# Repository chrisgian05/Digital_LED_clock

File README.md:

# Digital LED Clock

A 6-digit 7-segment clock (HH:MM:SS) built around an ATmega328P, an
external RTC, and a constant-current LED driver — split across two
custom PCBs I designed in KiCad. This was mostly an excuse to actually
use everything I've learned so far about digital electronics and
embedded C in one project I could see and touch, instead of another
breadboard that gets torn down at the end of the semester.

## What it does

- Shows time as HH:MM:SS across 6 seven-segment digits
- Keeps time with a DS3231 RTC (accurate even when the board is
  powered off, thanks to a coin cell)
- 4 buttons: set hour, set minute, reset seconds, and toggle to show
  the DS3231's built-in temperature reading instead of the time
- Multiplexed display — only one digit is physically powered at a
  time, cycled fast enough (~166Hz) that it looks fully lit

## Hardware

Two boards, connected by a short ribbon cable:

- **`clock_board`** — the "brains." ATmega328P, DS3231 RTC, a 74HC595
  shift register + 6 transistors for digit selection, an ISP header
  for programming, and the 4 push buttons.
- **`led_board`** — the "face." A TLC5916 constant-current LED driver
  feeding three 2-digit common-anode 7-segment modules (6 digits
  total), plus the transistor-switched power lines coming in from the
  clock board.

Full schematics and PCB layouts are in [`hardware/`](hardware/), one
subfolder per board. Both were designed from scratch in KiCad — no
dev-board shields, no premade modules other than the RTC/driver ICs
themselves.

## Firmware

Bare-metal AVR C — no Arduino core, straight `avr-libc` and direct
register access. I wanted to actually deal with I2C, timers, and
interrupts myself instead of hiding behind `Wire.h` and `digitalWrite`.

- **`twi.c`** — hardware I2C driver for talking to the DS3231
- **`ds3231.c`** — RTC register access (BCD conversion, get/set time, temperature)
- **`display.c`** — 7-segment font table + the Timer1 interrupt that handles
  digit multiplexing (bit-banging both the 74HC595 and TLC5916 shift chains)
- **`buttons.c`** — debounced button reads with auto-repeat on hold
- **`main.c`** — main loop tying it all together

All of it lives in [`firmware/`](firmware/), buildable with either the
included `Makefile` or `platformio.ini`.

## Status

Schematics and PCBs are designed; firmware is written and reviewed but
**not yet validated on the assembled board** (still waiting on
boards/soldering as of writing this). A couple of polarity assumptions
(digit-select active-high/low, segment driver active-high/low) are
flagged with `#define`s in `firmware/src/config.h` specifically because
they're easier to confirm with a multimeter on the real board than to
guess from a schematic.

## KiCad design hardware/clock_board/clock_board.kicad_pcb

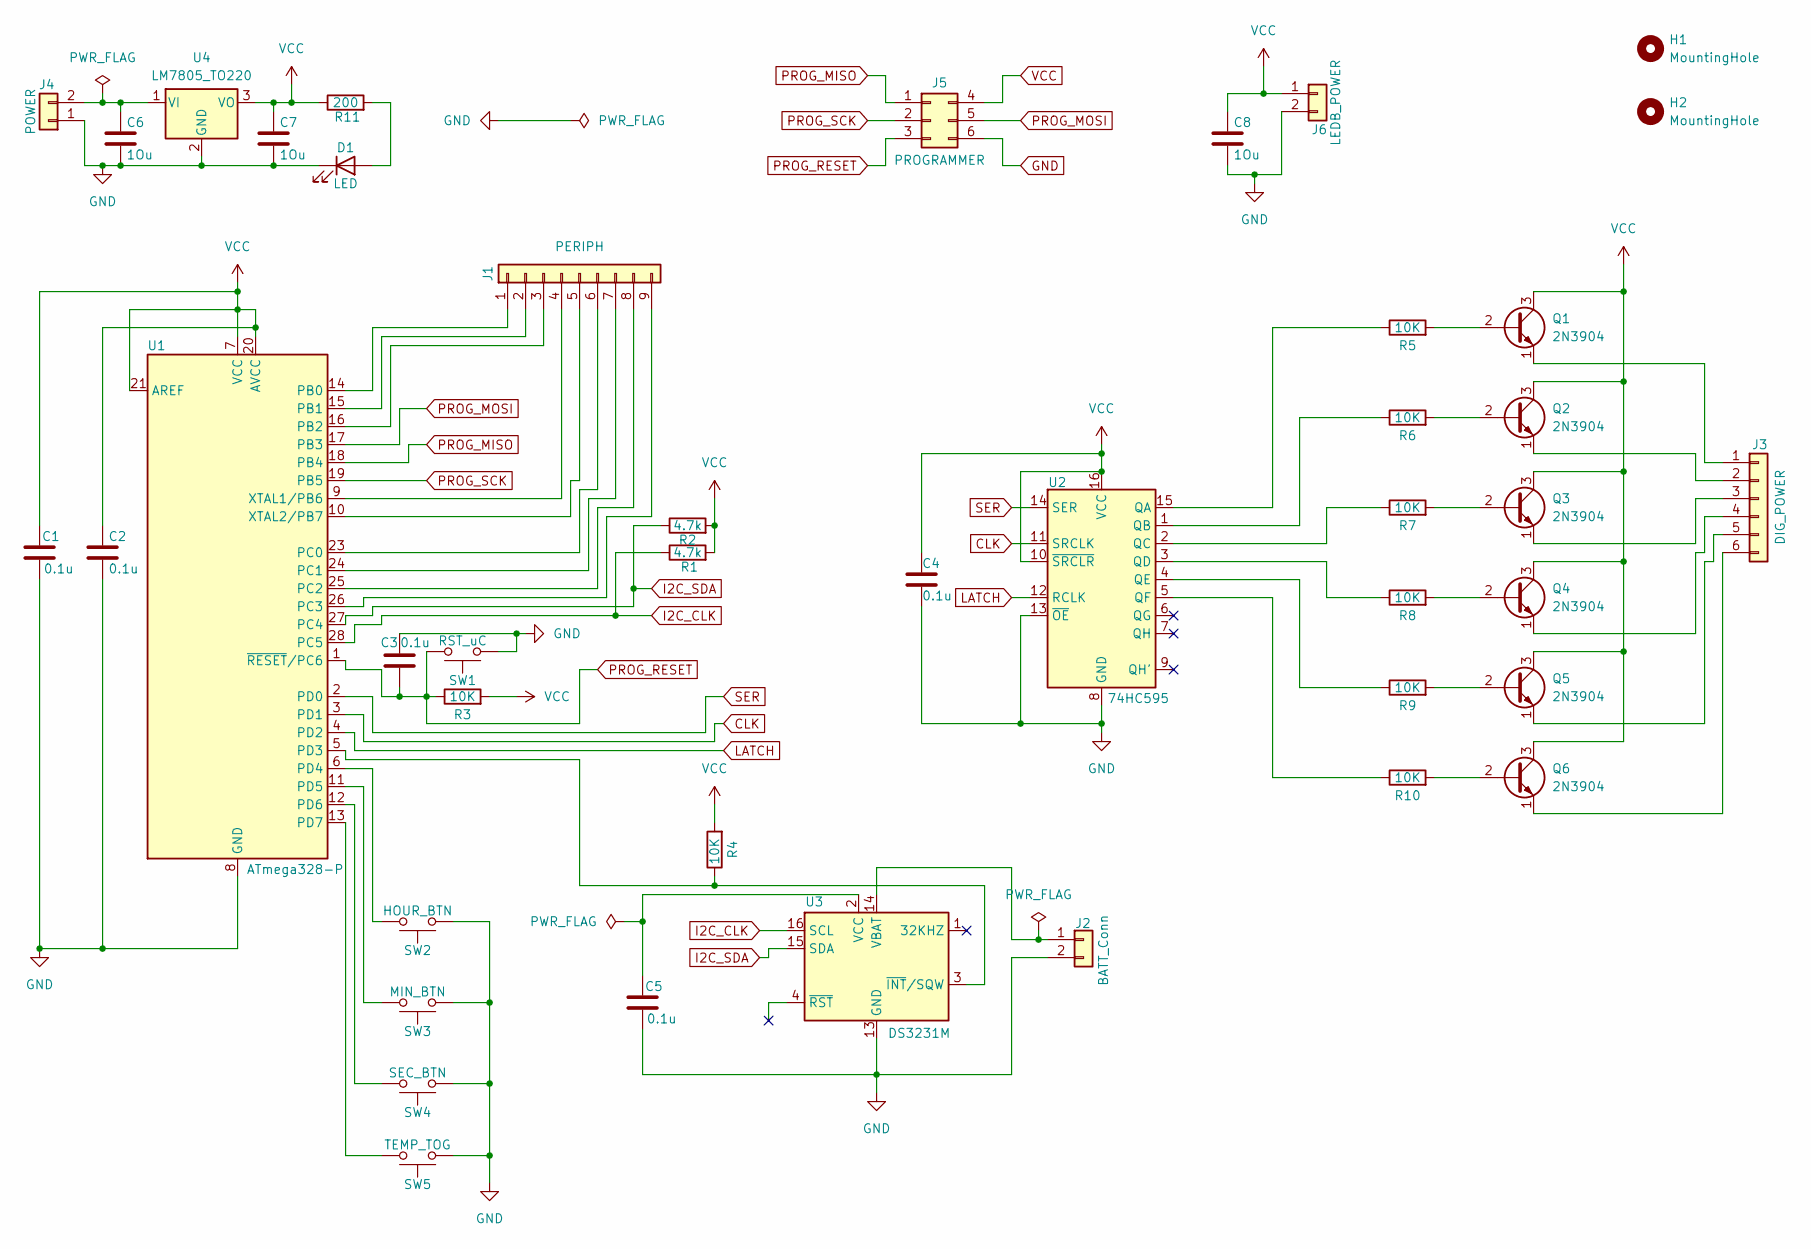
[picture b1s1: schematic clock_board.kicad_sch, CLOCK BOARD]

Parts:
C1, C2, C3, C4, C5: 0.1u; C_Disc_D3.8mm_W2.6mm_P2.50mm
C6, C7, C8: 1Ou; CP_Radial_D5.0mm_P2.00mm
D1: LED; LED_D5.0mm
H1, H2: MountingHole; MountingHole_3.2mm_M3_Pad
J1: PERIPH; PinHeader_1x09_P2.54mm_Vertical
J2: BATT_Conn; PinHeader_1x02_P2.54mm_Vertical
J3: DIG_POWER; PinHeader_1x06_P2.54mm_Vertical
J4: POWER; TerminalBlock_Phoenix_MKDS-1,5-2_1x02_P5.00mm_Horizontal
J5: PROGRAMMER; PinHeader_2x03_P2.54mm_Vertical
J6: LEDB_POWER; PinHeader_1x02_P2.54mm_Vertical
Q1, Q2, Q3, Q4, Q5, Q6: 2N3904; TO-92_Inline
R1, R2: 4.7k; R_Axial_DIN0207_L6.3mm_D2.5mm_P7.62mm_Horizontal
R3, R4, R5, R6, R7, R8, R9, R10: 10K; R_Axial_DIN0207_L6.3mm_D2.5mm_P7.62mm_Horizontal
R11: 200; R_Axial_DIN0207_L6.3mm_D2.5mm_P7.62mm_Horizontal
SW1: RST_uC; SW_PUSH_6mm_H5mm
SW2: HOUR_BTN; SW_PUSH_6mm_H5mm
SW3: MIN_BTN; SW_PUSH_6mm_H5mm
SW4: SEC_BTN; SW_PUSH_6mm_H5mm
SW5: TEMP_TOG; SW_PUSH_6mm_H5mm
U1: ATmega328-P; DIP-28_W7.62mm
U2: 74HC595; CERDIP-16_W7.62mm_SideBrazed
U3: DS3231M; SOIC-16W_7.5x10.3mm_P1.27mm
U4: LM7805_TO220; TO-220-3_Vertical

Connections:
CLK: U1.3 (PD1), U2.11 (SRCLK)
GND: C1.2, C2.2, C3.1, C4.2, C5.2, C6.2, C7.2, C8.2, D1.1 (K), J2.2, J4.1, J5.6, J6.2, SW1.1, SW2.1, SW3.1, SW4.1, SW5.1, U1.8 (GND), U1.22 (GND), U2.8 (GND), U2.13 (~OE), U3.5 (GND), U3.6 (GND), U3.7 (GND), U3.8 (GND), U3.9 (GND), U3.10 (GND), U3.11 (GND), U3.12 (GND), U3.13 (GND), U4.2 (GND)
I2C_CLK: R1.1, U1.28 (PC5), U3.16 (SCL)
I2C_SDA: R2.1, U1.27 (PC4), U3.15 (SDA)
LATCH: U1.4 (PD2), U2.12 (RCLK)
unnamed: D1.2 (A), R11.2
unnamed: J1.1, U1.14 (PB0)
unnamed: J1.2, U1.15 (PB1)
unnamed: J1.3, U1.16 (PB2)
unnamed: J1.4, U1.9 (XTAL1/PB6)
unnamed: J1.5, U1.10 (XTAL2/PB7)
unnamed: J1.6, U1.23 (PC0)
unnamed: J1.7, U1.24 (PC1)
unnamed: J1.8, U1.25 (PC2)
unnamed: J1.9, U1.26 (PC3)
unnamed: J2.1, U3.14 (VBAT)
unnamed: J3.1, Q1.1 (E)
unnamed: J3.2, Q2.1 (E)
unnamed: J3.3, Q3.1 (E)
unnamed: J3.4, Q4.1 (E)
unnamed: J3.5, Q5.1 (E)
unnamed: J3.6, Q6.1 (E)
unnamed: C6.1, J4.2, U4.1 (VI)
unnamed: Q1.2 (B), R5.2
unnamed: Q2.2 (B), R6.2
unnamed: Q3.2 (B), R7.2
unnamed: Q4.2 (B), R8.2
unnamed: Q5.2 (B), R9.2
unnamed: Q6.2 (B), R10.2
unnamed: R4.1, U1.5 (PD3), U3.3 (~INT/SQW)
unnamed: SW2.2, U1.6 (PD4)
unnamed: SW3.2, U1.11 (PD5)
unnamed: SW4.2, U1.12 (PD6)
unnamed: SW5.2, U1.13 (PD7)
unnamed: R5.1, U2.15 (QA)
unnamed: R6.1, U2.1 (QB)
unnamed: R7.1, U2.2 (QC)
unnamed: R8.1, U2.3 (QD)
unnamed: R9.1, U2.4 (QE)
unnamed: R10.1, U2.5 (QF)
unnamed: C5.1, U3.2 (VCC)
PROG_MISO: J5.1, U1.18 (PB4)
PROG_MOSI: J5.5, U1.17 (PB3)
PROG_RESET: C3.2, J5.3, R3.1, SW1.2, U1.1 (~RESET/PC6)
PROG_SCK: J5.2, U1.19 (PB5)
SER: U1.2 (PD0), U2.14 (SER)
VCC: C1.1, C2.1, C4.1, C7.1, C8.1, J5.4, J6.1, Q1.3 (C), Q2.3 (C), Q3.3 (C), Q4.3 (C), Q5.3 (C), Q6.3 (C), R1.2, R2.2, R3.2, R4.2, R11.1, U1.7 (VCC), U1.20 (AVCC), U1.21 (AREF), U2.10 (~SRCLR), U2.16 (VCC), U4.3 (VO)

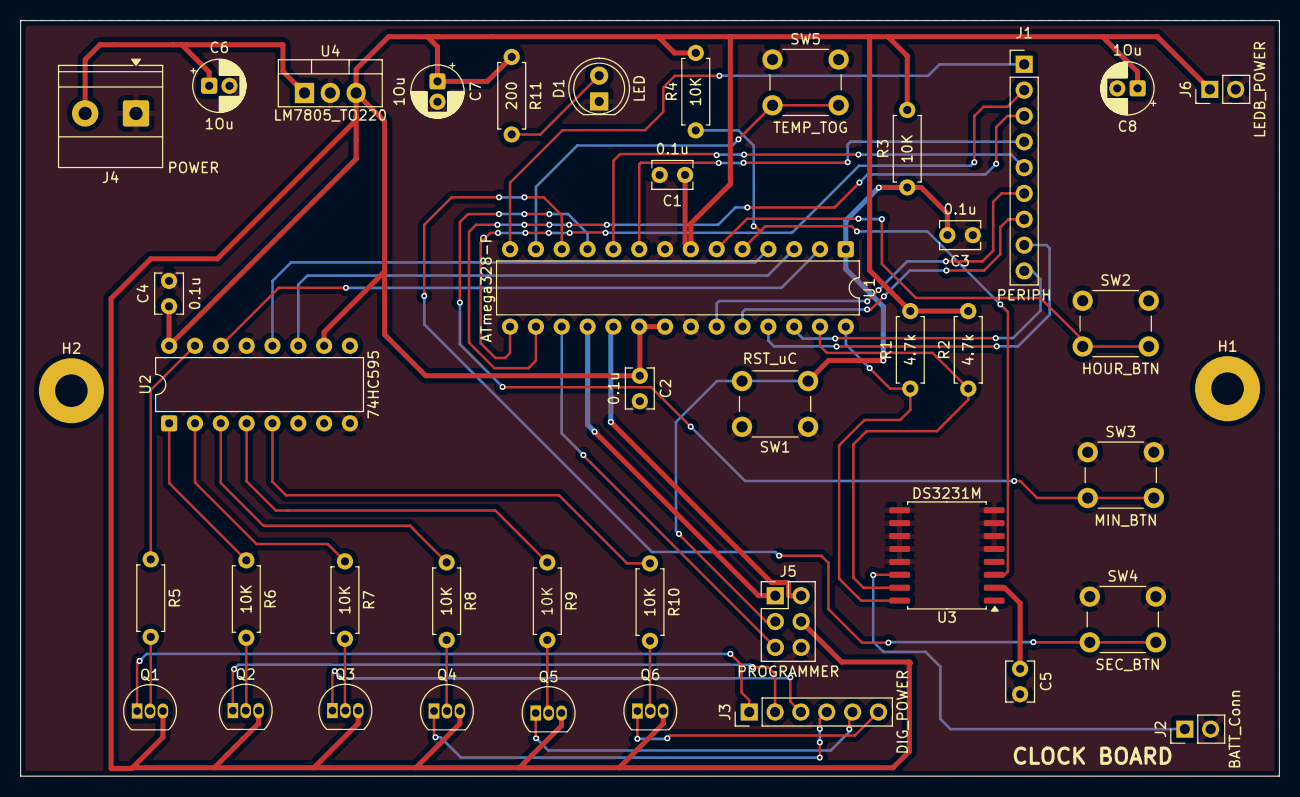
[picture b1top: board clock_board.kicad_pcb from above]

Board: 2 copper layers, 123.8 x 74.3 mm, 43 parts (0 on the bottom side), 47 nets.

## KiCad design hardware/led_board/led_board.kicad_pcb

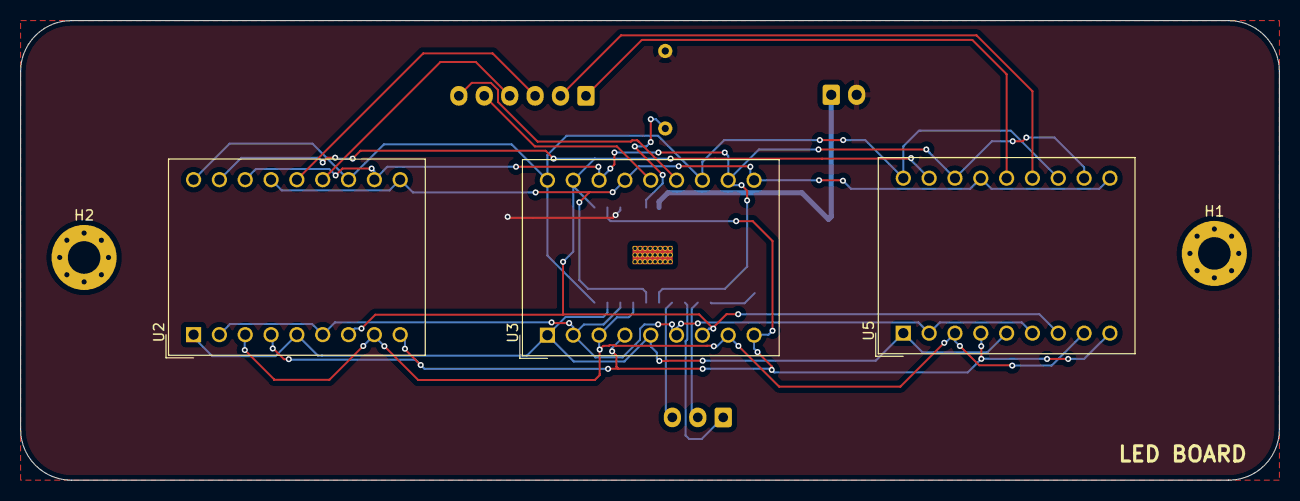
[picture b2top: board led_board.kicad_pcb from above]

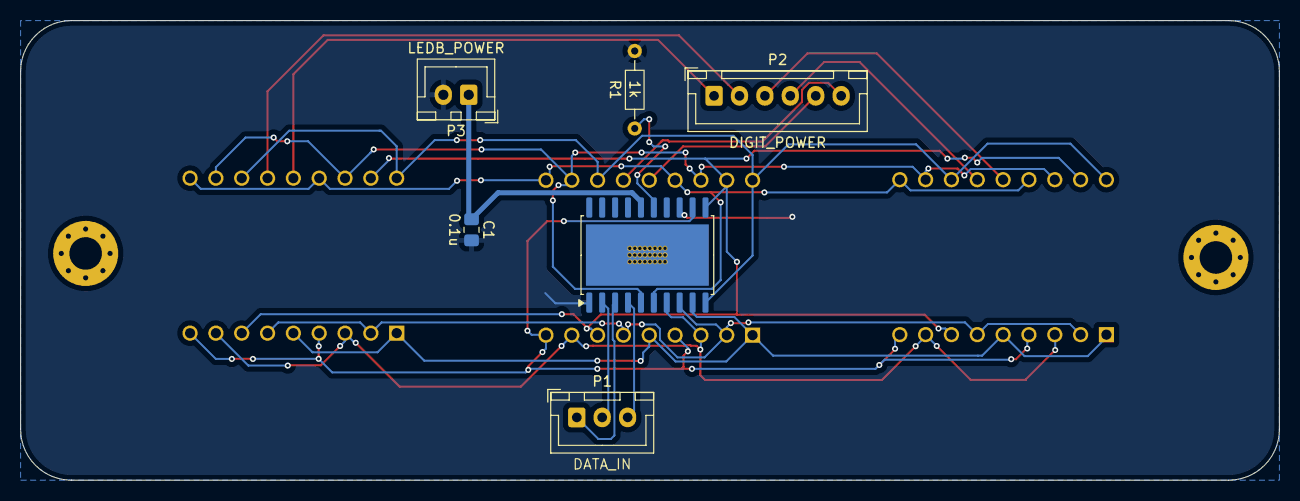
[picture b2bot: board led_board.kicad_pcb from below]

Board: 2 copper layers, 123.8 x 45.2 mm, 11 parts (6 on the bottom side), 20 nets.

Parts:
C1: 0.1u; C_0805_2012Metric_Pad1.18x1.45mm_HandSolder
H1, H2: MountingHole; MountingHole_3.2mm_M3_Pad_Via
P1: DATA_IN; JST_XH_B3B-XH-A_1x03_P2.50mm_Vertical
P2: DIGIT_POWER; JST_XH_B6B-XH-A_1x06_P2.50mm_Vertical
P3: LEDB_POWER; JST_XH_B2B-XH-A_1x02_P2.50mm_Vertical
R1: 1k; R_Axial_DIN0204_L3.6mm_D1.6mm_P7.62mm_Horizontal
U1: TLC5916; SO-20-1EP_7.52x12.825mm_P1.27mm_EP6.045x12.09mm_Mask3.56x4.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
U2, U3, U5: DA56-11CGKWA

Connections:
CLK: P1.1, U1.3 (CLK)
DIG1: P2.1, U5.14 (DIG1_CA)
DIG2: P2.2, U5.13 (DIG2_CA)
DIG3: P2.3, U2.14 (DIG1_CA)
DIG4: P2.4, U2.13 (DIG2_CA)
DIG5: P2.5, U3.14 (DIG1_CA)
DIG6: P2.6, U3.13 (DIG2_CA)
GND: C1.2, P3.2, R1.2, U1.1 (GND), U1.13 (~OE(ED2))
unnamed: R1.1, U1.15 (R-EXT)
SDA: P1.2, U1.2 (SDI)
SDL: P1.3, U1.4 (LE(ED1))
SEGA: U1.5 (~OUT0), U2.11 (DIG2_A), U2.16 (DIG1_A), U3.11 (DIG2_A), U3.16 (DIG1_A), U5.11 (DIG2_A), U5.16 (DIG1_A)
SEGB: U1.6 (~OUT1), U2.10 (DIG2_B), U2.15 (DIG1_B), U3.10 (DIG2_B), U3.15 (DIG1_B), U5.10 (DIG2_B), U5.15 (DIG1_B)
SEGC: U1.7 (~OUT2), U2.3 (DIG1_C), U2.8 (DIG2_C), U3.3 (DIG1_C), U3.8 (DIG2_C), U5.3 (DIG1_C), U5.8 (DIG2_C)
SEGD: U1.8 (~OUT3), U2.2 (DIG1_D), U2.6 (DIG2_D), U3.2 (DIG1_D), U3.6 (DIG2_D), U5.2 (DIG1_D), U5.6 (DIG2_D)
SEGDP: U1.12 (~OUT7), U2.4 (DP1), U2.9 (DP2), U3.4 (DP1), U3.9 (DP2), U5.4 (DP1), U5.9 (DP2)
SEGE: U1.9 (~OUT4), U2.1 (DIG1_E), U2.5 (DIG2_E), U3.1 (DIG1_E), U3.5 (DIG2_E), U5.1 (DIG1_E), U5.5 (DIG2_E)
SEGF: U1.10 (~OUT5), U2.12 (DIG2_F), U2.18 (DIG1_F), U3.12 (DIG2_F), U3.18 (DIG1_F), U5.12 (DIG2_F), U5.18 (DIG1_F)
SEGG: U1.11 (~OUT6), U2.7 (DIG2_G), U2.17 (DIG1_G), U3.7 (DIG2_G), U3.17 (DIG1_G), U5.7 (DIG2_G), U5.17 (DIG1_G)
VDD: C1.1, P3.1, U1.16 (VDD)

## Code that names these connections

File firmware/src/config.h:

#ifndef CONFIG_H
#define CONFIG_H

#ifndef F_CPU
#define F_CPU 8000000UL
#endif

/*74HC595 : digit select (clock board, local)*/
#define DIG595_PORT   PORTD
#define DIG595_DDR    DDRD
#define DIG595_SER    PD0   
#define DIG595_CLK    PD1   
#define DIG595_LATCH  PD2   

#define DIGIT_ACTIVE_HIGH 1

/*TLC5916 : segment data (over J1 PERIPH to the LED board)*/
#define SEG_PORT      PORTC
#define SEG_DDR       DDRC
#define SEG_SDI       PC0  
#define SEG_CLK       PC1   
#define SEG_LE        PC2  

#define SEGMENT_ACTIVE_HIGH 1 

/*Buttons (active LOW, using internal pull-ups)*/
#define BTN_PORT      PORTD
#define BTN_DDR       DDRD
#define BTN_PIN_REG   PIND
#define BTN_HOUR      PD4   
#define BTN_MIN       PD5   
#define BTN_SEC       PD6   
#define BTN_TEMP_TOG  PD7   

#define NUM_DIGITS 6

/* Refresh: each digit gets a 1 ms on-time slice -> ~166 Hz full-frame
 * refresh, well above the flicker threshold. Also used as a 1 kHz
 * system tick for button debouncing. */
#define REFRESH_TICK_HZ 1000UL

/* I2C bus speed to the DS3231 */
#define TWI_SCL_FREQ 100000UL /*100kHz*/

#endif 
